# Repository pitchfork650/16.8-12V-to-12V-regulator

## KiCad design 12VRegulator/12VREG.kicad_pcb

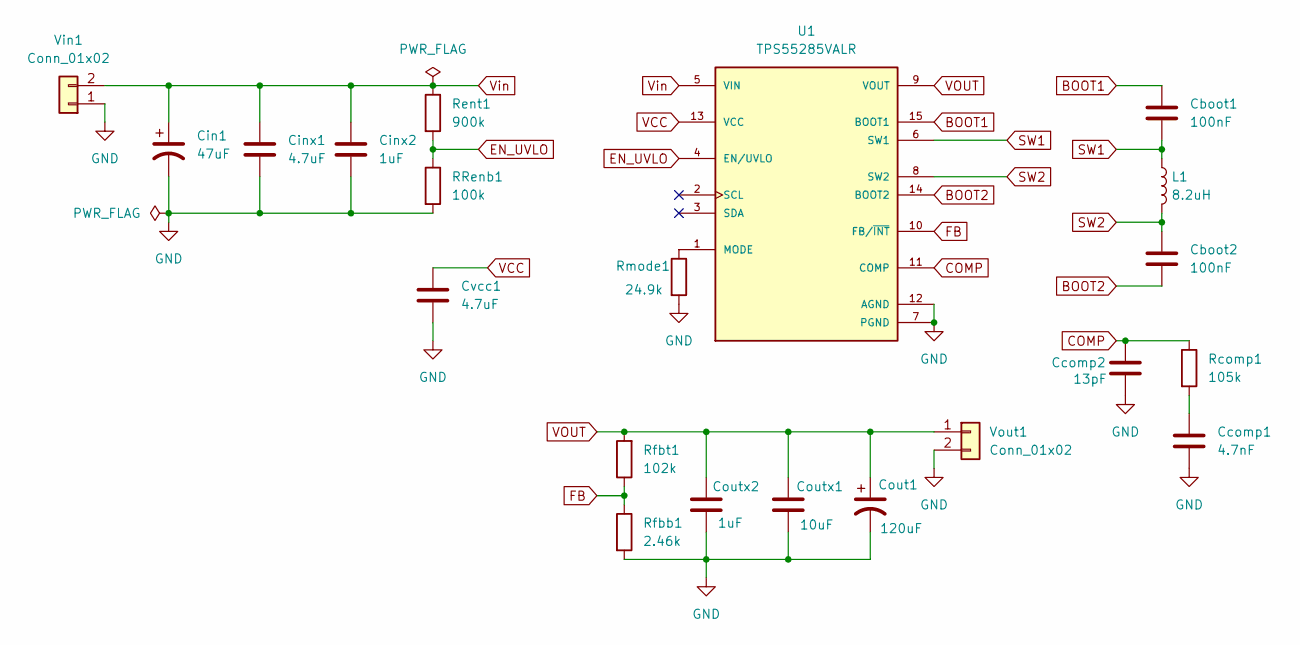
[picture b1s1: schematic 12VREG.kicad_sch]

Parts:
Cboot1, Cboot2: 100nF; C_0603_1608Metric_Pad1.08x0.95mm_HandSolder
Ccomp1: 4.7nF; C_0603_1608Metric_Pad1.08x0.95mm_HandSolder
Ccomp2: 13pF; C_0603_1608Metric_Pad1.08x0.95mm_HandSolder
Cin1: 47uF; CP_Elec_6.3x5.9
Cinx1: 4.7uF; C_1210_3225Metric_Pad1.33x2.70mm_HandSolder
Cinx2: 1uF; C_0603_1608Metric_Pad1.08x0.95mm_HandSolder
Cout1: 120uF; CP_Elec_6.3x5.9
Coutx1: 10uF; C_1210_3225Metric_Pad1.33x2.70mm_HandSolder
Coutx2: 1uF; C_0603_1608Metric_Pad1.08x0.95mm_HandSolder
Cvcc1: 4.7uF; C_0603_1608Metric_Pad1.08x0.95mm_HandSolder
L1: 8.2uH; L_Vishay_IHLP-2525
RRenb1: 100k; C_0603_1608Metric_Pad1.08x0.95mm_HandSolder
Rcomp1: 105k; C_0603_1608Metric_Pad1.08x0.95mm_HandSolder
Rent1: 900k; C_0603_1608Metric_Pad1.08x0.95mm_HandSolder
Rfbb1: 2.46k; C_0603_1608Metric_Pad1.08x0.95mm_HandSolder
Rfbt1: 102k; C_0603_1608Metric_Pad1.08x0.95mm_HandSolder
Rmode1: 24.9k; C_0603_1608Metric_Pad1.08x0.95mm_HandSolder
U1: TPS55285VALR; CONV_TPS55285VALR; MPN TPS55285VALR
Vin1: Conn_01x02; JST_PH_B2B-PH-SM4-TB_1x02-1MP_P2.00mm_Vertical
Vout1: Conn_01x02; JST_PH_B2B-PH-SM4-TB_1x02-1MP_P2.00mm_Vertical

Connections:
BOOT1: Cboot1.1, U1.15 (BOOT1)
BOOT2: Cboot2.2, U1.14 (BOOT2)
COMP: Ccomp2.1, Rcomp1.1, U1.11 (COMP)
EN_UVLO: RRenb1.1, Rent1.2, U1.4 (EN/UVLO)
FB: Rfbb1.1, Rfbt1.1, U1.10 (FB/~INT)
GND: Ccomp1.2, Ccomp2.2, Cin1.2, Cinx1.2, Cinx2.2, Cout1.2, Coutx1.2, Coutx2.2, Cvcc1.2, RRenb1.2, Rfbb1.2, Rmode1.2, U1.7 (PGND), U1.12 (AGND), Vin1.1, Vout1.2
unnamed: Ccomp1.1, Rcomp1.2
unnamed: Rmode1.1, U1.1 (MODE)
SW1: Cboot1.2, L1.1, U1.6 (SW1)
SW2: Cboot2.1, L1.2, U1.8 (SW2)
VCC: Cvcc1.1, U1.13 (VCC)
VOUT: Cout1.1, Coutx1.1, Coutx2.1, Rfbt1.2, U1.9 (VOUT), Vout1.1
Vin: Cin1.1, Cinx1.1, Cinx2.1, Rent1.1, U1.5 (VIN), Vin1.2

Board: 2 copper layers, 21 parts (0 on the bottom side), 13 nets, no tracks yet.

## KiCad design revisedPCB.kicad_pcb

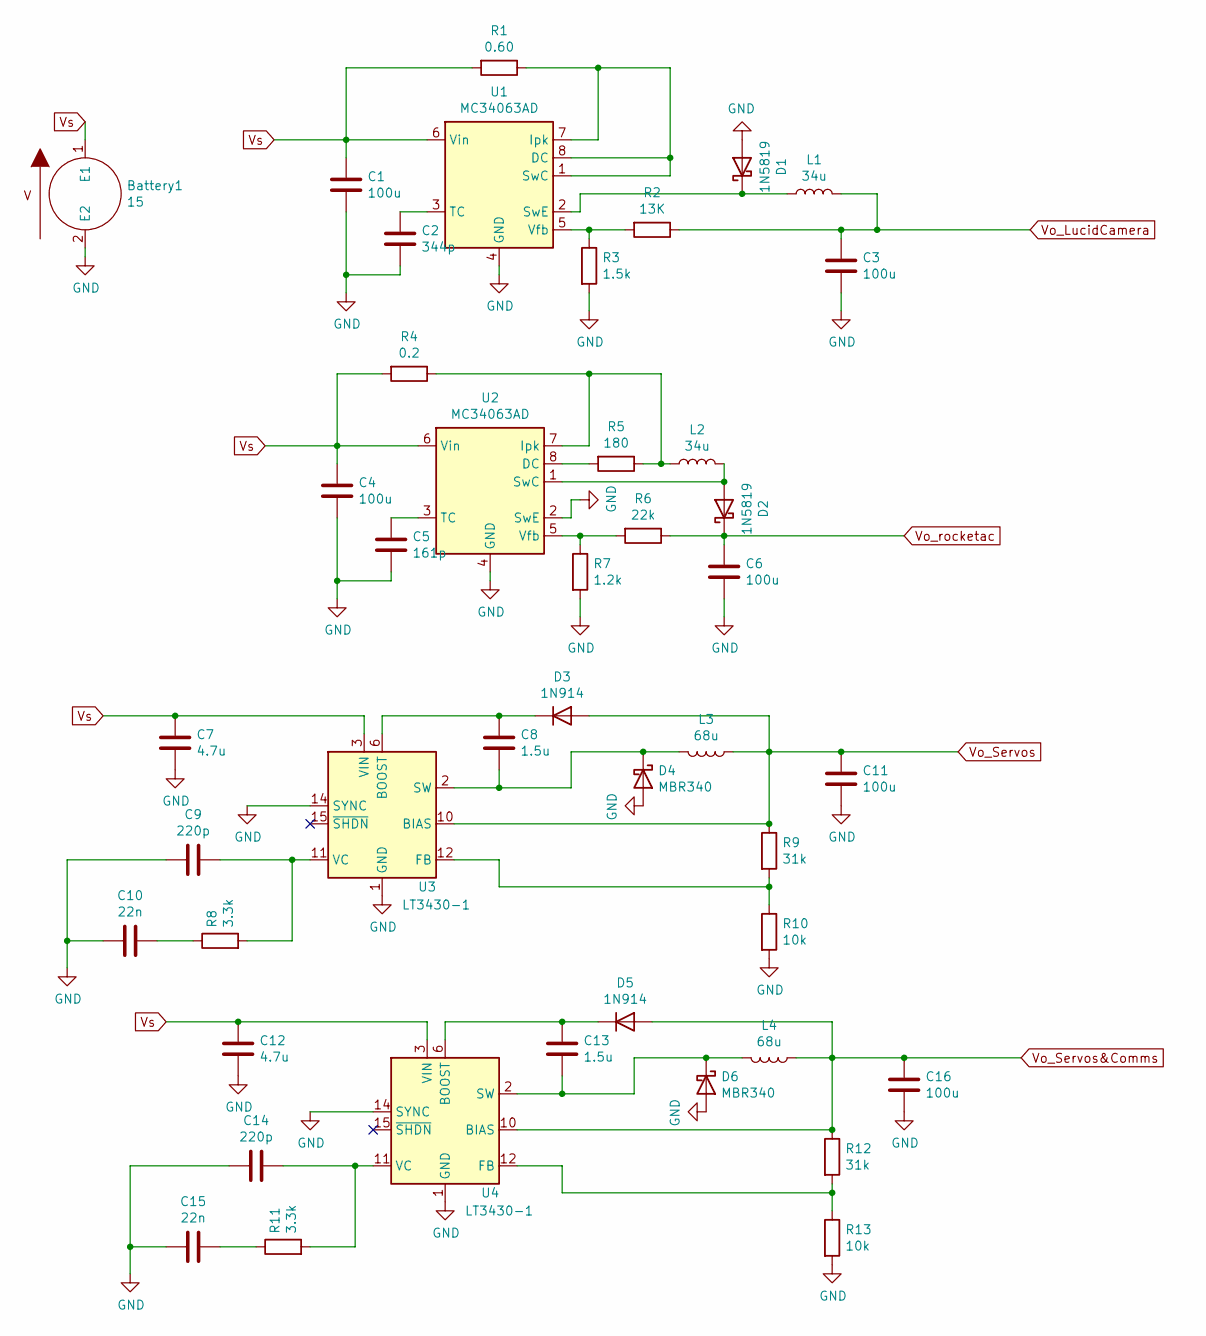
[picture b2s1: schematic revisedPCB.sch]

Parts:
Battery1: 15; AMASS_XT60-M_1x02_P7.20mm_Vertical
C1, C3, C4, C6, C11, C16: 100u; C_Elec_6.3x5.4
C2: 344p; C_0603_1608Metric
C5: 161p; C_0603_1608Metric
C7, C12: 4.7u; C_0603_1608Metric
C8, C13: 1.5u; C_0805_2012Metric
C9, C14: 220p; C_0603_1608Metric
C10, C15: 22n; C_0603_1608Metric
D1, D2: 1N5819; D_SOD-123
D3, D5: 1N914; D_DO-35_SOD27_P7.62mm_Horizontal
D4, D6: MBR340; D_DO-201AD_P15.24mm_Horizontal
L1, L2: 34u; L_Bourns-SRU8028_8.0x8.0mm
L3, L4: 68u; L_Vishay_IHLP-6767
R1: 0.60; R_0805_2012Metric
R2: 13K; R_0603_1608Metric
R3: 1.5k; R_0603_1608Metric
R4: 0.2; R_0805_2012Metric
R5: 180; R_0603_1608Metric
R6: 22k; R_0603_1608Metric
R7: 1.2k; R_0603_1608Metric
R8, R11: 3.3k; R_0603_1608Metric
R9, R12: 31k; R_0603_1608Metric
R10, R13: 10k; R_0603_1608Metric
U1, U2: MC34063AD; SOIC-8_3.9x4.9mm_P1.27mm
U3, U4: LT3430-1; TSSOP-16-1EP_4.4x5mm_P0.65mm

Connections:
GND: Battery1.2 (E2), C1.2, C2.2, C3.2, C4.2, C5.2, C6.2, C7.2, C9.2, C10.2, C11.2, C12.2, C14.2, C15.2, C16.2, D1.2 (A), D4.2 (A), D6.2 (A), R3.2, R7.2, R10.2, R13.2, U1.4 (GND), U2.2 (SwE), U2.4 (GND), U3.1 (GND), U3.8 (GND), U3.9 (GND), U3.14 (SYNC), U3.16 (GND), U3.17 (GND), U4.1 (GND), U4.8 (GND), U4.9 (GND), U4.14 (SYNC), U4.16 (GND), U4.17 (GND)
unnamed: C2.1, U1.3 (TC)
unnamed: C5.1, U2.3 (TC)
unnamed: C8.1, D3.1 (K), U3.6 (BOOST)
unnamed: C8.2, D4.1 (K), L3.2, U3.2 (SW), U3.5 (SW)
unnamed: C9.1, R8.2, U3.11 (VC)
unnamed: C10.1, R8.1
unnamed: C13.1, D5.1 (K), U4.6 (BOOST)
unnamed: C13.2, D6.1 (K), L4.2, U4.2 (SW), U4.5 (SW)
unnamed: C14.1, R11.2, U4.11 (VC)
unnamed: C15.1, R11.1
unnamed: D1.1 (K), L1.1, U1.2 (SwE)
unnamed: D2.2 (A), L2.2, U2.1 (SwC)
unnamed: L2.1, R4.1, R5.1, U2.7 (Ipk)
unnamed: R1.1, U1.1 (SwC), U1.7 (Ipk), U1.8 (DC)
unnamed: R2.2, R3.1, U1.5 (Vfb)
unnamed: R5.2, U2.8 (DC)
unnamed: R6.2, R7.1, U2.5 (Vfb)
unnamed: R9.2, R10.1, U3.12 (FB)
unnamed: R12.2, R13.1, U4.12 (FB)
Vo_LucidCamera: C3.1, L1.2, R2.1
Vo_Servos: C11.1, D3.2 (A), L3.1, R9.1, U3.10 (BIAS)
Vo_Servos&Comms: C16.1, D5.2 (A), L4.1, R12.1, U4.10 (BIAS)
Vo_rocketac: C6.1, D2.1 (K), R6.1
Vs: Battery1.1 (E1), C1.1, C4.1, C7.1, C12.1, R1.2, R4.2, U1.6 (Vin), U2.6 (Vin), U3.3 (VIN), U3.4 (VIN), U4.3 (VIN), U4.4 (VIN)

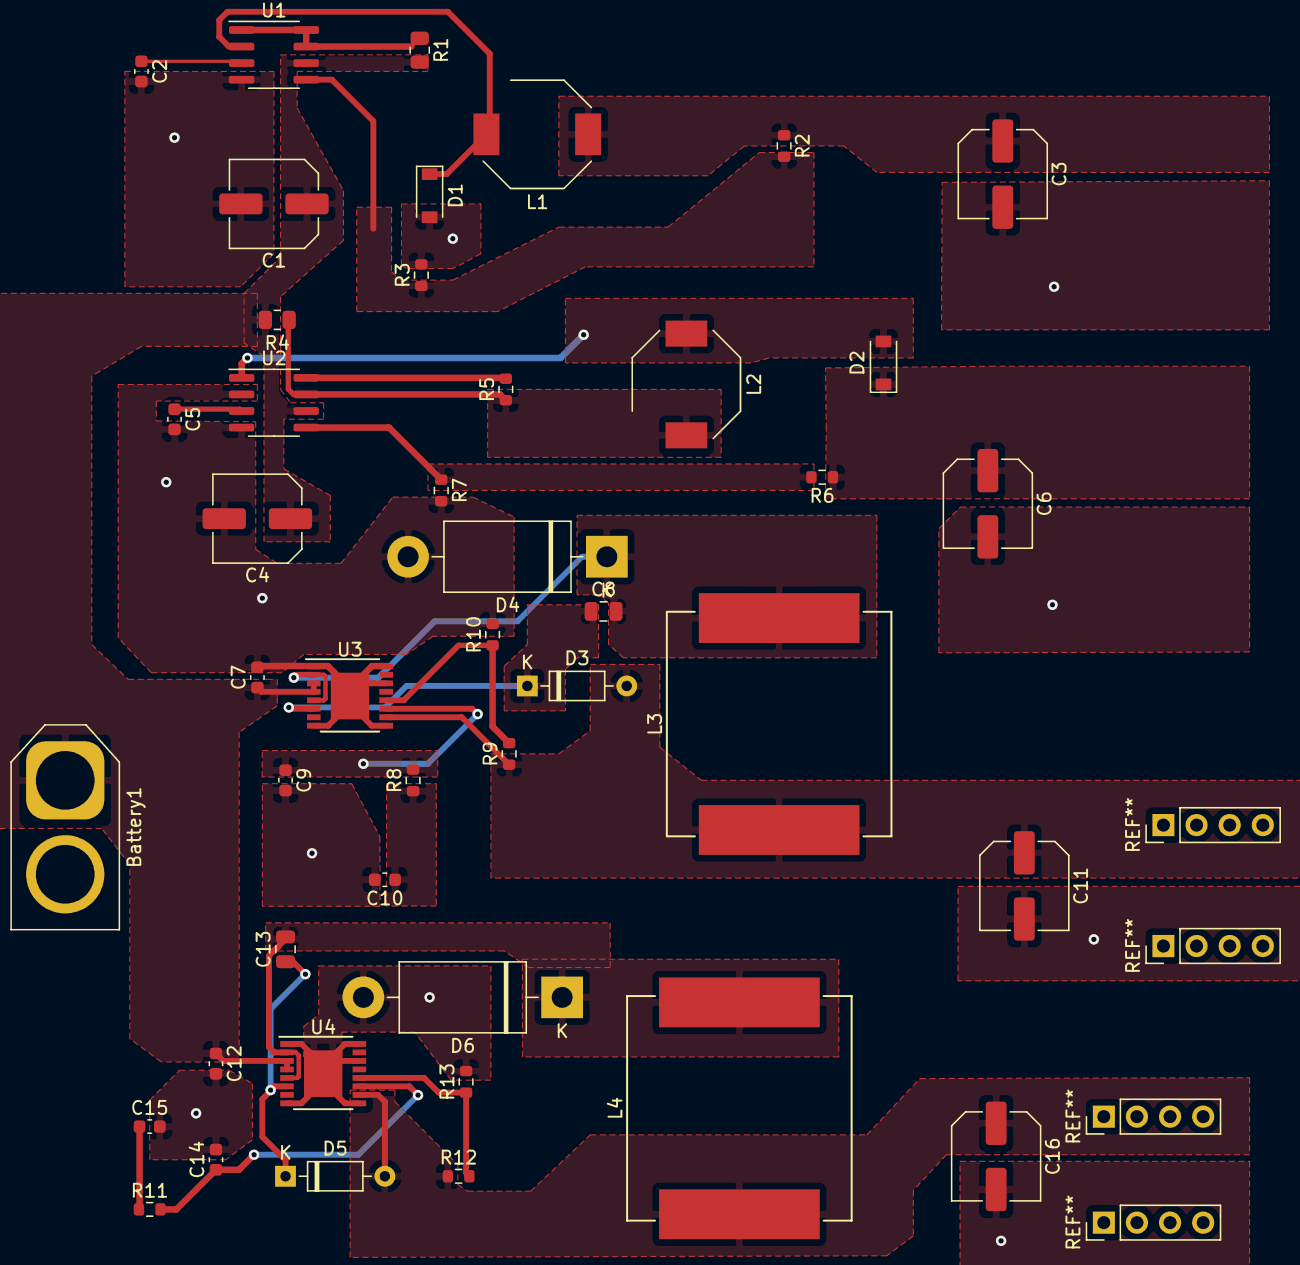
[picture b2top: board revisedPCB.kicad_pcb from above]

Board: 2 copper layers, 44 parts (0 on the bottom side), 25 nets.

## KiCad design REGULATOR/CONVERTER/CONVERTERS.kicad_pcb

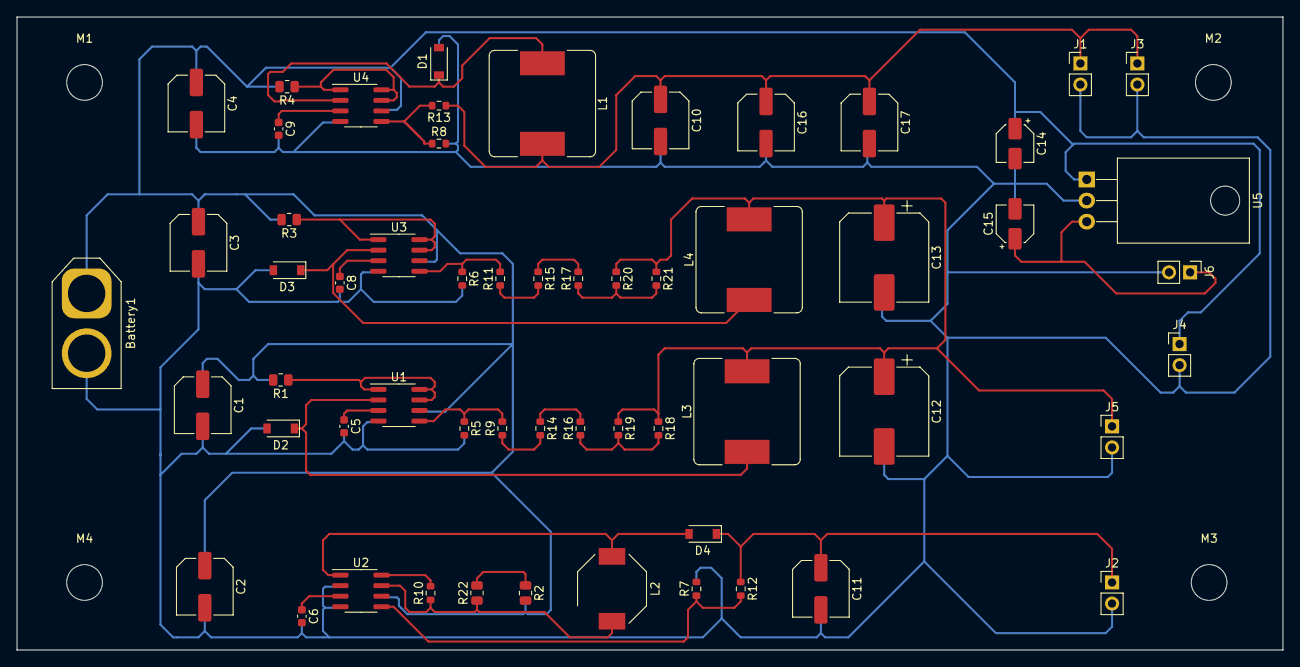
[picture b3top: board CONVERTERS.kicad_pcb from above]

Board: 2 copper layers, 152.4 x 76.2 mm, 62 parts (0 on the bottom side), 30 nets.

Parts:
Battery1: 15; AMASS_XT60-M_1x02_P7.20mm_Vertical
C1, C2, C3, C4, C10, C11, C16, C17: 100u; C_Elec_6.3x5.4
C5, C8: 240p; C_0603_1608Metric
C6, C9: 160p; C_0603_1608Metric
C12, C13: 390u; CP_Elec_10x10.5
C14: 0.33u; CP_Elec_4x4.5
C15: 0.1u; CP_Elec_4x4.5
D1, D2, D3, D4: 1N5819; D_SOD-123
J1, J2, J3, J4, J5, J6: Conn_01x02_Male; PinHeader_1x02_P2.54mm_Vertical
L1, L3, L4: 12u; L_Bourns_SRR1260
L2: 36u; L_Bourns-SRU8028_8.0x8.0mm
M1, M2, M3, M4: MountingHole_4.3mm_M4
R1, R2, R3, R4, R22: 0.1; R_0805_2012Metric
R5, R6, R7, R8, R14, R15, R16, R17, R18, R19, R20, R21: 1.2k; R_0603_1608Metric
R9, R11, R13: 3.6k; R_0603_1608Metric
R10: 180; R_0603_1608Metric
R12: 22k; R_0603_1608Metric
U1, U2, U3, U4: MC34063AD; SOIC-8_3.9x4.9mm_P1.27mm
U5: L7812; TO-220-3_Horizontal_TabDown

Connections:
GND: Battery1.2, C1.2, C2.2, C3.2, C4.2, C5.2, C6.2, C8.2, C9.2, C10.2, C11.2, C12.2, C13.2, C14.2, C15.2, C16.2, C17.2, D1.2, D2.2, D3.2, J1.2, J2.2, J3.2, J4.2, J5.2, J6.2, R5.2, R6.2, R7.2, R8.2, U1.4, U2.2, U2.4, U3.4, U4.4, U5.2
unnamed: C5.1, U1.3
unnamed: C6.1, U2.3
unnamed: C8.1, U3.3
unnamed: C9.1, U4.3
unnamed: D1.1, L1.1, U4.2
unnamed: D2.1, L3.1, U1.2
unnamed: D3.1, L4.1, U3.2
unnamed: D4.2, L2.2, U2.1
unnamed: L2.1, R10.1, R22.1, U2.7
unnamed: R1.1, U1.1, U1.7, U1.8
unnamed: R2.1, R22.2
unnamed: R3.1, U3.1, U3.7, U3.8
unnamed: R4.1, U4.1, U4.7, U4.8
unnamed: R5.1, R9.2, U1.5
unnamed: R10.2, U2.8
unnamed: R11.1, R15.2
unnamed: R6.1, R11.2, U3.5
unnamed: R7.1, R12.2, U2.5
unnamed: R8.1, R13.2, U4.5
unnamed: R14.1, R16.2
unnamed: R9.1, R14.2
unnamed: R15.1, R17.2
unnamed: R16.1, R18.2, R19.2
unnamed: R17.1, R20.2, R21.2
Vo_camera: C12.1, C13.1, J5.1, L3.2, L4.2, R18.1, R19.1, R20.1, R21.1
Vo_jetson: C15.1, J6.1, U5.3
Vo_rocketac: C11.1, D4.1, J2.1, R12.1
Vo_servo: C10.1, C16.1, C17.1, J1.1, J3.1, L1.2, R13.1
Vs: Battery1.1, C1.1, C2.1, C3.1, C4.1, C14.1, J4.1, R1.2, R2.2, R3.2, R4.2, U1.6, U2.6, U3.6, U4.6, U5.1

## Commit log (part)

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2020-11-29 Add regulator spreadsheet.
2020-11-29 Change regulator file to .csv.
2021-02-27 Updated amount of components
2021-03-03 Add KiCad schematics
2021-03-03 Add blank file
2021-03-03 Add CONVERTER folder w/o .git
2021-03-03 removed converter dir
2021-03-03 added converter dir
2021-03-06 Update diode to surface mount
2021-03-06 Route the PCB
2021-03-10 Fix Vs & GND copper traces
2021-04-06 Fixed connector layout on schematic
2021-04-06 Fix connectors on PCB
2021-04-19 Fix mounting hole layout
2021-04-19 Fix wiring
2022-04-22 2022 update
2022-05-06 add new BOM
2022-05-14 add lt3430-1 boms
